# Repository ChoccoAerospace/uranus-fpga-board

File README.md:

# uranus-fpga-board

Uranus is a goated planet idk. FPGAs are also cool i guess (very cool).

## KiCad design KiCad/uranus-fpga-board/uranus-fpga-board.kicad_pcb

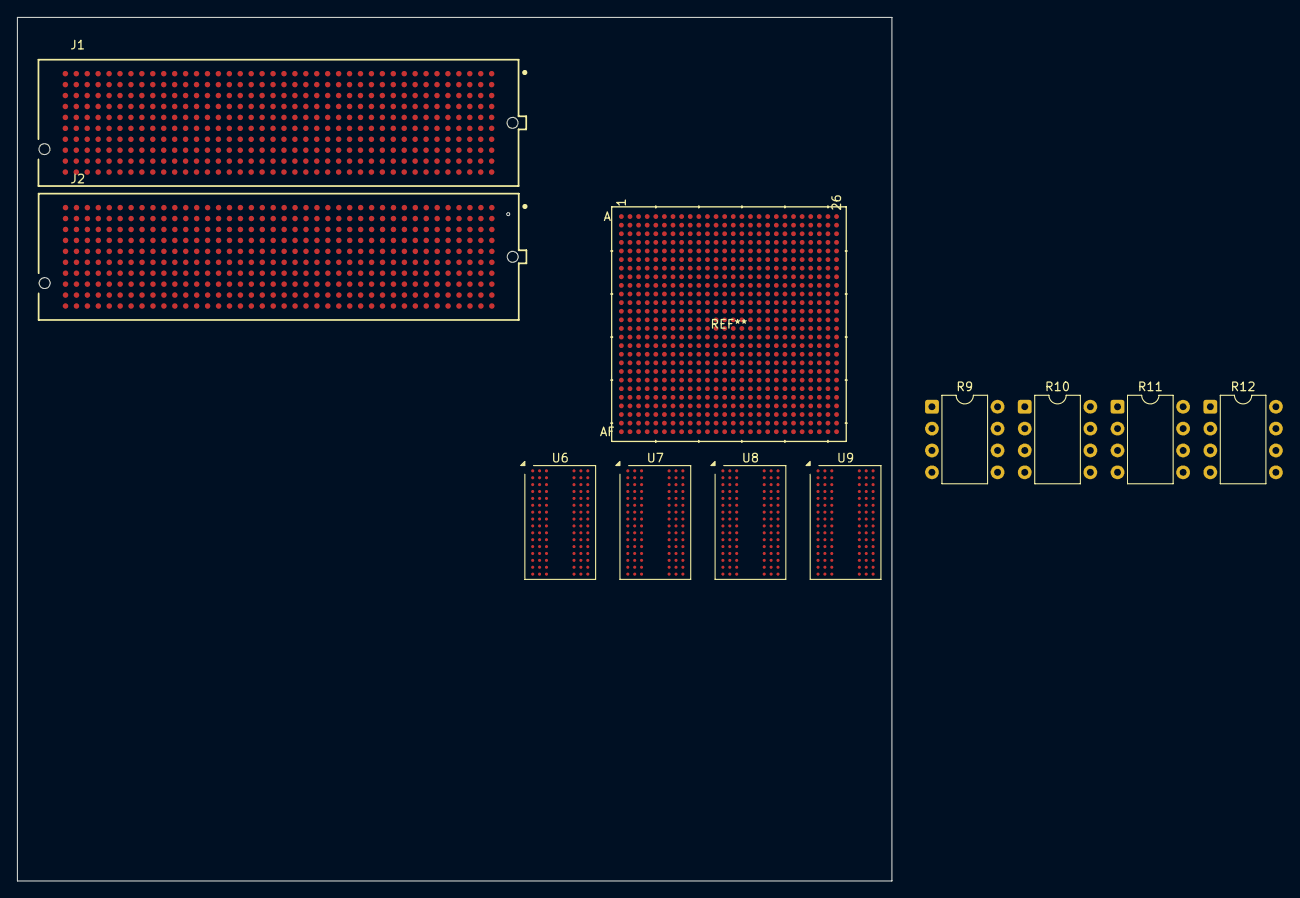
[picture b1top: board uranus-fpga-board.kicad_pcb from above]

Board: 8 copper layers, 101.6 x 100.3 mm, 10 parts (0 on the bottom side), 34 nets, no tracks yet.

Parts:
J1, J2: ASP-134488-01; SAMTEC_ASP-134488-01
R9, R10, R11, R12: 240Ω; DIP-8_W7.62mm
U6, U7, U8, U9: AS4C256M16D3; FBGA-96_8x13mm_Layout9x16_P0.8mm

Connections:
+1V5: U6.A1 (VDDQ), U6.A8 (VDDQ), U6.B2 (VDD), U6.C1 (VDDQ), U6.C9 (VDDQ), U6.D2 (VDDQ), U6.D9 (VDD), U6.E9 (VDDQ), U6.F1 (VDDQ), U6.G7 (VDD), U6.H2 (VDDQ), U6.H9 (VDDQ), U6.K2 (VDD), U6.K8 (VDD), U6.N1 (VDD), U6.N9 (VDD), U6.R1 (VDD), U6.R9 (VDD), U7.A1 (VDDQ), U7.A8 (VDDQ), U7.B2 (VDD), U7.C1 (VDDQ), U7.C9 (VDDQ), U7.D2 (VDDQ), U7.D9 (VDD), U7.E9 (VDDQ), U7.F1 (VDDQ), U7.G7 (VDD), U7.H2 (VDDQ), U7.H9 (VDDQ), U7.K2 (VDD), U7.K8 (VDD), U7.N1 (VDD), U7.N9 (VDD), U7.R1 (VDD), U7.R9 (VDD), U8.A1 (VDDQ), U8.A8 (VDDQ), U8.B2 (VDD), U8.C1 (VDDQ), U8.C9 (VDDQ), U8.D2 (VDDQ), U8.D9 (VDD), U8.E9 (VDDQ), U8.F1 (VDDQ), U8.G7 (VDD), U8.H2 (VDDQ), U8.H9 (VDDQ), U8.K2 (VDD), U8.K8 (VDD), U8.N1 (VDD), U8.N9 (VDD), U8.R1 (VDD), U8.R9 (VDD), U9.A1 (VDDQ), U9.A8 (VDDQ), U9.B2 (VDD), U9.C1 (VDDQ), U9.C9 (VDDQ), U9.D2 (VDDQ), U9.D9 (VDD), U9.E9 (VDDQ), U9.F1 (VDDQ), U9.G7 (VDD), U9.H2 (VDDQ), U9.H9 (VDDQ), U9.K2 (VDD), U9.K8 (VDD), U9.N1 (VDD), U9.N9 (VDD), U9.R1 (VDD), U9.R9 (VDD)
A0: U6.N3 (A0), U7.N3 (A0), U8.N3 (A0), U9.N3 (A0)
A1: U6.P7 (A1), U7.P7 (A1), U8.P7 (A1), U9.P7 (A1)
A2: U6.P3 (A2), U7.P3 (A2), U8.P3 (A2), U9.P3 (A2)
A3: U6.N2 (A3), U7.N2 (A3), U8.N2 (A3), U9.N2 (A3)
A4: U6.P8 (A4), U7.P8 (A4), U8.P8 (A4), U9.P8 (A4)
A5: U6.P2 (A5), U7.P2 (A5), U8.P2 (A5), U9.P2 (A5)
A6: U6.R8 (A6), U7.R8 (A6), U8.R8 (A6), U9.R8 (A6)
A7: U6.R2 (A7), U7.R2 (A7), U8.R2 (A7), U9.R2 (A7)
A8: U6.T8 (A8), U7.T8 (A8), U8.T8 (A8), U9.T8 (A8)
A9: U6.R3 (A9), U7.R3 (A9), U8.R3 (A9), U9.R3 (A9)
A10: U6.L7 (A10/AP), U7.L7 (A10/AP), U8.L7 (A10/AP), U9.L7 (A10/AP)
A11: U6.R7 (A11), U7.R7 (A11), U8.R7 (A11), U9.R7 (A11)
A12: U6.N7 (A12/~BC), U7.N7 (A12/~BC), U8.N7 (A12/~BC), U9.N7 (A12/~BC)
BA0: U6.M2 (BA0), U7.M2 (BA0), U8.M2 (BA0), U9.M2 (BA0)
BA1: U6.N8 (BA1), U7.N8 (BA1), U8.N8 (BA1), U9.N8 (BA1)
BA2: U6.M3 (BA2), U7.M3 (BA2), U8.M3 (BA2), U9.M3 (BA2)
CAS: U6.K3 (~CAS), U7.K3 (~CAS), U8.K3 (~CAS), U9.K3 (~CAS)
CKE: U6.K9 (CKE), U7.K9 (CKE), U8.K9 (CKE), U9.K9 (CKE)
CK_N: U6.K7 (~CK), U7.K7 (~CK), U8.K7 (~CK), U9.K7 (~CK)
CK_P: U6.J7 (CK), U7.J7 (CK), U8.J7 (CK), U9.J7 (CK)
CS: U6.L2 (~CS), U7.L2 (~CS), U8.L2 (~CS), U9.L2 (~CS)
GND: R9.1, R10.1, R11.1, R12.1, U6.A9 (VSS), U6.B1 (VSSQ), U6.B3 (VSS), U6.B9 (VSSQ), U6.D1 (VSSQ), U6.D8 (VSSQ), U6.E1 (VSS), U6.E2 (VSSQ), U6.E8 (VSSQ), U6.F9 (VSSQ), U6.G1 (VSSQ), U6.G8 (VSS), U6.G9 (VSSQ), U6.J2 (VSS), U6.J8 (VSS), U6.M1 (VSS), U6.M9 (VSS), U6.P1 (VSS), U6.P9 (VSS), U6.T1 (VSS), U6.T9 (VSS), U7.A9 (VSS), U7.B1 (VSSQ), U7.B3 (VSS), U7.B9 (VSSQ), U7.D1 (VSSQ), U7.D8 (VSSQ), U7.E1 (VSS), U7.E2 (VSSQ), U7.E8 (VSSQ), U7.F9 (VSSQ), U7.G1 (VSSQ), U7.G8 (VSS), U7.G9 (VSSQ), U7.J2 (VSS), U7.J8 (VSS), U7.M1 (VSS), U7.M9 (VSS), U7.P1 (VSS), U7.P9 (VSS), U7.T1 (VSS), U7.T9 (VSS), U8.A9 (VSS), U8.B1 (VSSQ), U8.B3 (VSS), U8.B9 (VSSQ), U8.D1 (VSSQ), U8.D8 (VSSQ), U8.E1 (VSS), U8.E2 (VSSQ), U8.E8 (VSSQ), U8.F9 (VSSQ), U8.G1 (VSSQ), U8.G8 (VSS), U8.G9 (VSSQ), U8.J2 (VSS), U8.J8 (VSS), U8.M1 (VSS), U8.M9 (VSS), U8.P1 (VSS), U8.P9 (VSS), U8.T1 (VSS), U8.T9 (VSS), U9.A9 (VSS), U9.B1 (VSSQ), U9.B3 (VSS), U9.B9 (VSSQ), U9.D1 (VSSQ), U9.D8 (VSSQ), U9.E1 (VSS), U9.E2 (VSSQ), U9.E8 (VSSQ), U9.F9 (VSSQ), U9.G1 (VSSQ), U9.G8 (VSS), U9.G9 (VSSQ), U9.J2 (VSS), U9.J8 (VSS), U9.M1 (VSS), U9.M9 (VSS), U9.P1 (VSS), U9.P9 (VSS), U9.T1 (VSS), U9.T9 (VSS)
unnamed: R9.2, U6.L8 (ZQ)
unnamed: R10.2, U7.L8 (ZQ)
unnamed: R11.2, U8.L8 (ZQ)
unnamed: R12.2, U9.L8 (ZQ)
ODT: U6.K1 (ODT), U7.K1 (ODT), U8.K1 (ODT), U9.K1 (ODT)
RAS: U6.J3 (~RAS), U7.J3 (~RAS), U8.J3 (~RAS), U9.J3 (~RAS)
RESET: U6.T2 (~RESET), U7.T2 (~RESET), U8.T2 (~RESET), U9.T2 (~RESET)
VREF_0: U6.H1 (VREFDQ), U6.M8 (VREFCA), U7.H1 (VREFDQ), U7.M8 (VREFCA)
VREF_1: U8.H1 (VREFDQ), U8.M8 (VREFCA)
VREF_2: U9.H1 (VREFDQ), U9.M8 (VREFCA)
WE: U6.L3 (~WE), U7.L3 (~WE), U8.L3 (~WE), U9.L3 (~WE)
